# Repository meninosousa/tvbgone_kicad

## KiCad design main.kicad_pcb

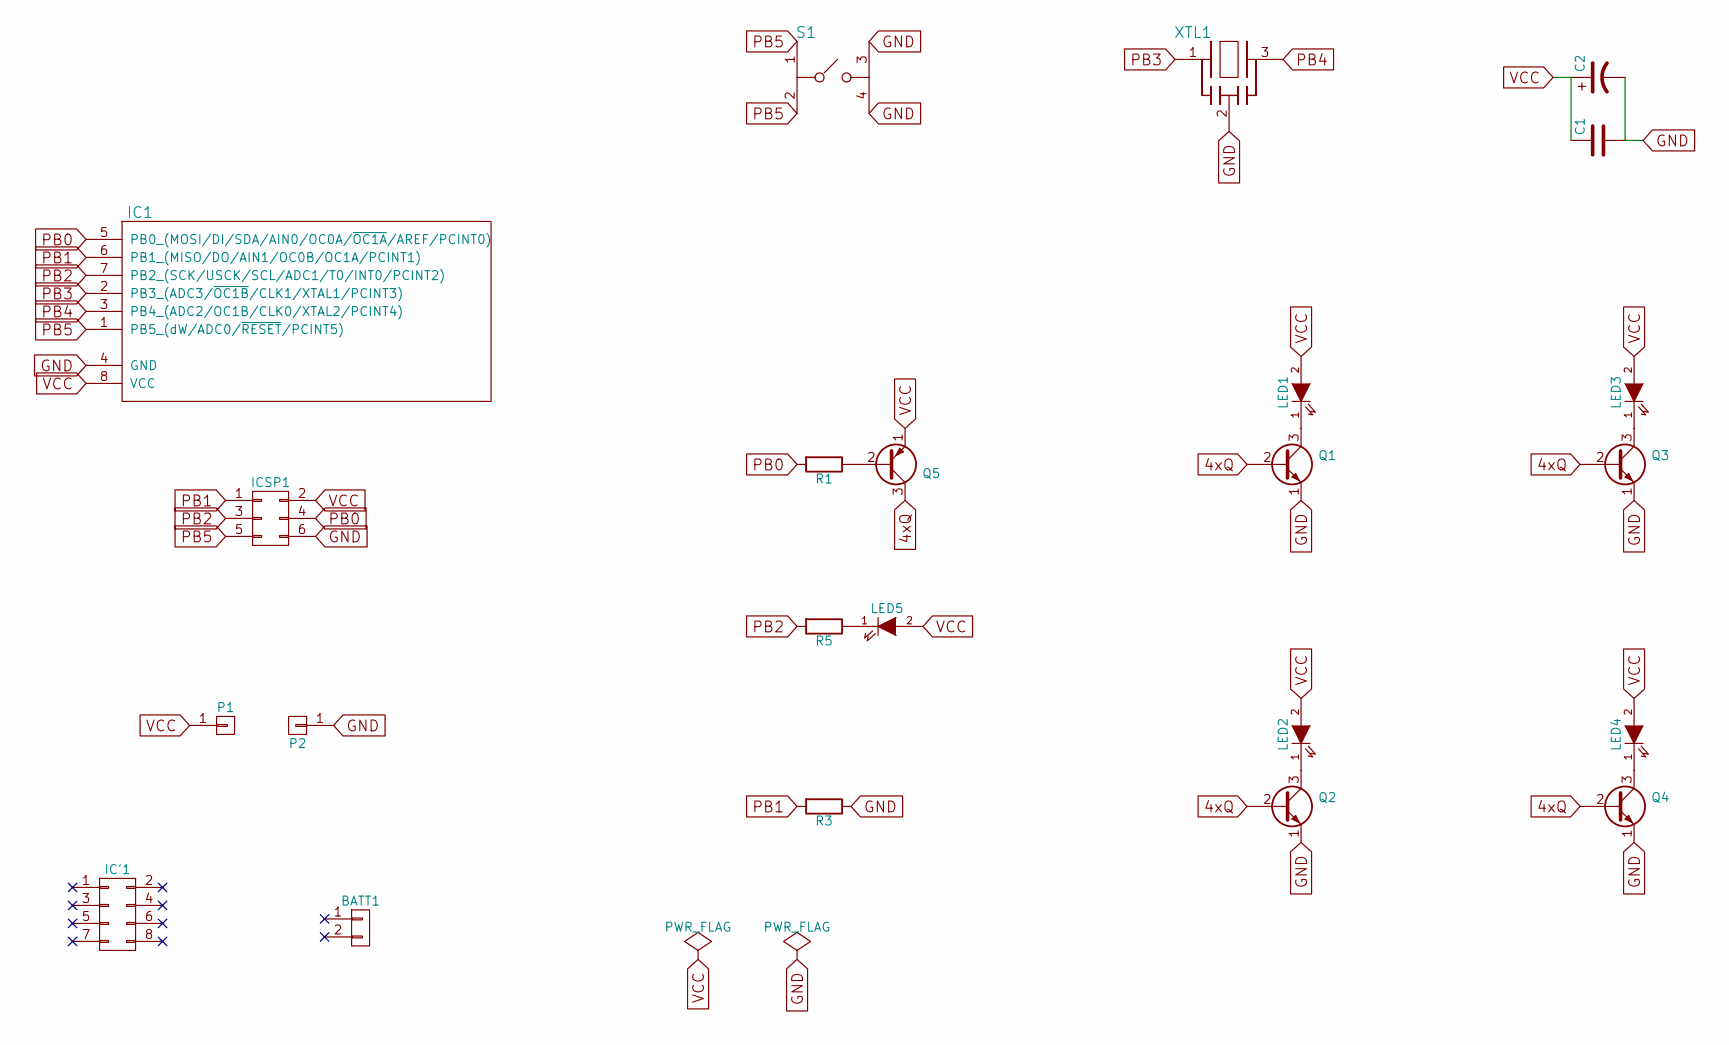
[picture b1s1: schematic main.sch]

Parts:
BATT1: 2xAA; Digikey 36-2463-ND
C1: 0.1uF; C_Disc_D3_P2.5; Digikey 399-4151-ND
C2: >=220uF >=6.3V; C_Radial_D5_L11_P2; Digikey 493-1004-ND
IC1: DIP-8_W7.62mm; Digikey ATTINY85V-10PU-ND
IC'1: Digikey ED3044-5-ND
ICSP1: Pin_Header_Straight_2x03; Digikey 952-1921-ND
LED1, LED4: LED-5MM; Digikey 1080-1082-ND
LED2, LED3: LED-5MM; Digikey 1080-1080-ND
LED5: Green 3mm; LED-3MM; Digikey 1125-1186-ND
P1, P2: Pin_Header_Straight_1x01; Digikey S1112EC-01-ND
Q1, Q2, Q3, Q4: TO-92_Molded_Narrow; Digikey PN2222ATFCT-ND
Q5: TO-92_Molded_Narrow; Digikey PN2907-ND
R1, R5: 1K 1/4W 5%; Resistor_Horizontal_RM10mm; Digikey CF14JT1K00CT-ND
R3: 10K 1/4 5%; Resistor_Horizontal_RM10mm; Digikey CF14JT10K0CT-ND
S1: 6mm; TE-Connectivity-Alcoswitch-Switches_1825910-6; Digikey 450-1804-ND
XTL1: 8MHz; Murata-Electronics-North-America_CSTLS8M00G53-B0; Digikey 490-1212-ND

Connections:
4xQ: Q1.2 (B), Q2.2 (B), Q3.2 (B), Q4.2 (B), Q5.3 (C)
GND: C1.2, C2.2, IC1.4 (GND), ICSP1.6, P2.1, Q1.1 (E), Q2.1 (E), Q3.1 (E), Q4.1 (E), R3.1, S1.3, S1.4, XTL1.2
unnamed: LED1.1 (K), Q1.3 (C)
unnamed: LED2.1 (K), Q2.3 (C)
unnamed: LED3.1 (K), Q3.3 (C)
unnamed: LED4.1 (K), Q4.3 (C)
unnamed: LED5.1 (K), R5.1
unnamed: Q5.2 (B), R1.1
PB0: IC1.5 (PB0_(MOSI/DI/SDA/AIN0/OC0A/~OC1A~/AREF/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), ICSP1.4, R1.2
PB1: IC1.6 (PB1_(MISO/DO/AIN1/OC0B/OC1A/PCINT1)), ICSP1.1, R3.2
PB2: IC1.7 (PB2_(SCK/USCK/SCL/ADC1/T0/INT0/PCINT2)), ICSP1.3, R5.2
PB3: IC1.2 (PB3_(ADC3/~OC1B~/CLK1/XTAL1/PCINT3)), XTL1.1
PB4: IC1.3 (PB4_(ADC2/OC1B/CLK0/XTAL2/PCINT4)), XTL1.3
PB5: IC1.1 (PB5_(dW/ADC0/~RESET~/PCINT5)), ICSP1.5, S1.1, S1.2
VCC: C1.1, C2.1, IC1.8 (VCC), ICSP1.2, LED1.2 (A), LED2.2 (A), LED3.2 (A), LED4.2 (A), LED5.2 (A), P1.1, Q5.1 (E)

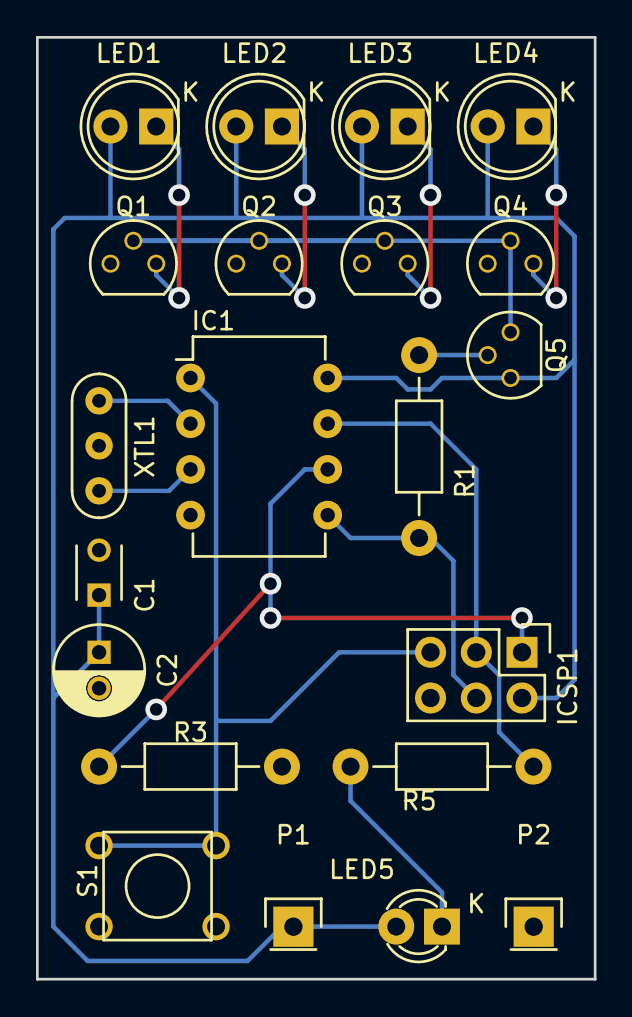
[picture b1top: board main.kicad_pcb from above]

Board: 2 copper layers, 31.0 x 52.3 mm, 21 parts (0 on the bottom side), 15 nets.

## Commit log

2016-06-14 :boom::camel: Added .gitattributes & .gitignore files
2016-06-14 last version
    so far
2016-06-15 new vias
    bigger and better for cnc
2016-06-15 logo
    pacman logo added
2016-06-15 more logo
    more packman
2016-06-15 nao sei
    pld
2016-06-20 last so far
    yes pls
2016-06-20 adjustments
    done
